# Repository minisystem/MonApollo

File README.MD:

=============================
Programmable Analog Monosynth
=============================
Prototype 
-------------
Digital Board
-------------

Digital board tested and working. SPI LED driving and switch reading tested. ADC pot reading but there is some cross-talk on
potentiometer ADC channels. Allowing sufficient settling time at ADC node between reads seems to mostly remedy this
to <= 1 LSB.

------------
Analog Board
------------
DAC S&H tested and working. There is some cross-talk (<= 10mV) on adjacent CV traces, but these are currently floating. Need to test
for crosstalk again once CV targets are installed.

NOISE/LFO/S&H tested and working, except for multiplexer latch problem mentioned below. Noise gain needed to be adjusted by
changing R180 to 10K and R181 to 750K (two 1.5M 0603s stacked in parallel). Also LFO module needede R3 (on module board) changed to 270K from 1M to get proper adjustment of sine/tri symmetry.
Sine symmetry is too 'pointy' on negative transition. Perhaps D1 and D2 need to be matched for Vf?

Bugs discovered thus far:

1. 7905 power regular pin error. Power supply rendered useless by this, so board requires external supply
2. LFO DG408 demultiplexer address lines are not latched, making LFO source addressing useless. Need to add 74LC75
latch in next revision.
2. C107 S&H sample cap footprint is 0805, but there are no NP0 or film caps in this footprint. Tried X7R and there was too much
droop. Through-hole film cap is in there now and droop is better, but still about 50-60 mV per second. This could be 
related to layout and leakage across PCB traces. A second look at layout shows definite room for improvement.
3. Glide circuit: Q6 PNP matched pair BCM857BS was flipped in schematic, swapping collectors and emitters. Good grief! Can't be salavaged
by a bodge, so will have to move on to VCO mod depth control and revisit glide in next PCB revision.
4. Glide slew caps C47 and C48 are currently 0603 but need to be 0805 or 1206 or even throughhole if film caps are to be used.

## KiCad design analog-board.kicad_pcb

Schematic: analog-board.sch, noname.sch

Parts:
C1, C8, C10, C18, C19, C20, C21, C22, C92, C93, C94, C96, C97, C98, C99, C103, C104: 1µ
C2, C9, C11, C15, C17, C23, C24, C25, C26, C27, C28, C29, C30, C31, C32, C33, C34, C35, C36, C37, C38, C39, C40, C41, C42, C43, C44, C45, C46, C85, C88, C114, C115, C117, C118, C119, C120, C121, C122, C123, C124, C125, C126, C127, C128, C129, C130, C131, C132, C133: 0.1µ
C3, C4, C5, C12, C13, C14, C16, C81, C82, C83, C84, C86, C87, C101: 10p
C6, C7: 5.6p
C47, C48: 470n
C49, C50, C51, C52, C53, C54, C55, C56, C57, C58, C59, C60, C61, C62, C63, C64, C65, C66, C67, C68, C69, C70, C71, C72, C73, C74, C75, C76, C77, C78, C79, C80: 0.01µ
C89, C91: 47μ
C90, C107: 100n
C95: 10μ
C100, C134: 22µ
C102: 4.7n
C105, C106, C108, C109: 1000µ
C110: 1.5n
C111: 100pF
C112, C113, C116: 2.2µ
C135: 47p
D1, D2, D3, D4, D5, D6, D7, D8, D9, D10: DIODE
D11, D12: LED
D13: 1N4148
EG1, EG2: EG
J1: AC IN
J2: OUT
J3: CONN_20X2
LFO1: VCO
P2: CONN_01X02
Q1, Q2, Q3, Q4, Q5, Q7, Q8, Q9, Q10, Q11, Q12, Q13, Q14, Q15, Q16, Q20: 2N3906
Q6: BCM857BS
Q17, Q18: NPN
Q19: J111
R1, R2, R3, R4, R5, R26, R27, R28, R29, R30, R79, R80, R95, R96, R97, R104, R110, R111, R112, R113, R130, R131, R132, R133, R134, R151, R183, R198: 12K
R6, R7, R8, R9, R13, R16, R17, R19, R20, R21, R87, R88, R89, R90, R98, R101, R114, R115, R118, R119, R122, R123, R124, R125, R135, R140, R188, R190: 510
R10, R11, R12, R24, R25, R91, R92, R102, R116, R117, R120, R121, R145, R174, R192: 2.2M
R14, R15, R18, R126, R127, R128, R129: 68K
R22, R23, R93, R94, R103, R146, R170, R171, R196: 18K
R31, R32, R33, R34, R38, R99, R100, R105, R136, R137, R138, R139, R152, R200: 47K
R35, R36, R37, R141, R142, R143, R144: 91K
R39, R189, R193, R206, R207: 1K
R40, R41, R42, R147, R148, R149, R150: 270K
R43, R44, R45, R46, R47, R48, R49, R50, R51, R52, R53, R54, R55, R56, R57, R58, R59, R60, R61, R62, R63, R64, R65, R66, R67, R70, R71, R72, R73, R74, R75, R77, R78, R81, R84, R153, R154, R155, R156, R157, R158, R159, R163, R164, R165, R167, R173, R175, R176, R184, R199, R202, R204: 100K
R68: 33K
R69: 1K 3300ppm/K
R76: 39K
R82, R83, R85, R86: 4.7K
R106, R107, R108, R109: 100K
R160, R205: 10K
R161: 3.3M
R162: 390K
R166, R168: 27K
R169: 680K**
R172: 47K
R177: 150K
R178: 22
R179, R185, R191, R201, R211, R213, R215: 10K
R180: 15K
R181, R203: 470K
R182: 120K
R186: 1.5K
R187, R195: 18K
R194: 20K
R197: 2.2meg
R208, R209: 220K
R210: 3.3K
R212, R214: 9.1K
R216: 270K
R217: 22K
TP1, TP2, TP3, TP4, TP5, TP6, TP7, TP8, TP9, TP10, TP11, TP12, TP13, TP14, TP15, TP16, TP17, TP18, TP19, TP20, TP21, TP22, TP23, TP24, TP25, TP26, TP27, TP28, TP29, TP30, TP31, TP32, TP33, TP34, TP35, TP36, TP37, TP38, TP39: CONN_1
TR1, TR2, TR3, TR4, TR5, TR8, TR9, TR10, TR11, TR12, TR13, TR14, TR15, TR16, TR18, TR19, TR21, TR23: 100K
TR6, TR7, TR17, TR20, TR22: 20K
U1, U2, U3, U18, U19, U29, U30, U32: LM13700
U4, U12: DG212B
U5, U8, U22, U23, U24, U25, U27, U28, U31, U33, U34, U35, U39: TL074-
U6: AD5556
U7, U15, U21, U26: TL072-
U9: AD8672
U10: ADR01
U11: DG212B; TSSOP-16
U13, U14, U16, U17, U45: DG408
U20: 74HC75
U36: 74LV573; Digikey SN74LV573APWR
U38, U41: 0 - 10V
U40: DG419
U42: 10 - 0V
U43: LM7812
U44: LM7912
U46: 7805
VCFA1: VCF_VCA
VCO1, VCO2: VCO

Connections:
+5V: C1.1 (+), C2.1, C88.1, C116.1 (+), TP35.1, U4.12 (VL), U6.28 (VDD), U11.12 (VL), U12.12 (VL), U20.5 (VCC), U36.20 (VCC), U40.5 (VCC), U46.3 (VO)
+12V: C8.1 (+), C9.1, C17.1, C18.1 (+), C21.1, C22.1, C25.1, C26.1, C27.1, C29.1, C31.1, C33.1, C35.1, C39.1, C40.1, C41.1, C43.1, C45.1, C85.1, C94.1, C97.1, C98.1, C104.1, C112.1 (+), C115.1, C118.1, C120.1, C122.1, C124.1, C126.1, C128.1, C130.1, C132.1, D9.2 (K), EG1.1 (V+), EG2.1 (V+), J3.1, J3.2, LFO1.2 (V+), R26.2, R27.2, R28.2, R29.2, R30.2, R76.2, R95.2, R96.2, R104.2, R130.2, R131.2, R133.2, R134.2, R151.2, R178.1, R184.1, R198.2, R206.1, R216.2, TP33.1, TR1.3, TR2.3, TR3.3, TR4.3, TR5.3, TR8.3, TR9.3, TR10.3, TR11.3, TR12.3, TR13.3, TR14.3, TR15.3, TR16.3, TR18.1, TR21.1, TR23.3, U1.11 (V+), U2.11 (V+), U3.11 (V+), U4.13 (V+), U5.4 (V+), U7.8 (V+), U8.4 (V+), U9.8 (V+), U10.3 (VIN), U11.13 (V+), U12.13 (V+), U13.13 (V+), U14.13 (V+), U15.8 (V+), U16.13 (V+), U17.13 (V+), U18.11 (V+), U19.11 (V+), U21.8 (V+), U22.4 (V+), U23.4 (V+), U24.4 (V+), U25.4 (V+), U26.8 (V+), U27.4 (V+), U28.4 (V+), U29.11 (V+), U30.11 (V+), U31.4 (V+), U32.11 (V+), U33.4 (V+), U34.4 (V+), U35.4 (V+), U39.4 (V+), U40.4 (V+), U43.3 (VO), U45.2 (EN), U45.13 (V+), U46.1 (VI), VCFA1.4 (V+), VCO1.2 (V+), VCO2.2 (V+)
-12V: C10.2 (-), C11.2, C19.1, C20.1, C23.1, C24.1, C28.2, C30.2, C32.2, C34.2, C36.2, C37.1, C38.1, C42.2, C44.2, C46.2, C93.1, C96.1, C99.1, C103.1, C113.2 (-), C114.1, C117.2, C119.2, C121.2, C123.2, C125.2, C127.2, C129.2, C131.2, C133.2, D10.1 (A), EG1.3 (V-), EG2.3 (V-), LFO1.3 (V-), R162.2, R207.2, R208.1, R209.1, TP34.1, TR1.1, TR2.1, TR3.1, TR4.1, TR5.1, TR8.1, TR9.1, TR10.1, TR11.1, TR12.1, TR13.1, TR14.1, TR15.1, TR16.1, TR18.3, TR19.1, TR21.3, TR23.1, U1.6 (V-), U2.6 (V-), U3.6 (V-), U4.4 (V-), U5.11 (V-), U7.4 (V-), U8.11 (V-), U9.4 (V-), U11.4 (V-), U12.4 (V-), U13.3 (V-), U14.3 (V-), U15.4 (V-), U16.3 (V-), U17.3 (V-), U18.6 (V-), U19.6 (V-), U21.4 (V-), U22.11 (V-), U23.11 (V-), U24.11 (V-), U25.11 (V-), U26.4 (V-), U27.11 (V-), U28.11 (V-), U29.6 (V-), U30.6 (V-), U31.11 (V-), U32.6 (V-), U33.11 (V-), U34.11 (V-), U35.11 (V-), U39.11 (V-), U44.3 (VO), U45.3 (V-), VCFA1.5 (V-), VCO1.3 (V-), VCO2.3 (V-)
/DAC0: J3.35, U6.6 (DB0)
/DAC1: J3.34, U6.5 (DB1)
/DAC2: J3.33, U6.4 (DB2)
/DAC3: J3.32, U6.3 (DB3)
/DAC4: J3.31, U6.2 (DB4)
/DAC5: J3.30, U6.1 (DB5)
/DAC6: J3.29, U6.27 (DB6)
/DAC7: J3.28, U6.26 (DB7)
/DAC8: J3.25, U6.25 (DB8)
/DAC9: J3.24, U6.24 (DB9)
/DAC10: J3.23, U6.23 (DB10)
/DAC11: J3.22, U6.22 (DB11)
/DAC12: J3.21, U6.21 (DB12)
/DAC13: J3.20, U6.20 (DB13)
/VREF: C15.1, TP9.1, U6.11 (R1), U10.4 (VOUT)
AMP LFO AMT CV: R146.1, U28.8, U28.9 (-)
ANALOG SW LATCH: J3.36, U36.11 (Load)
CUTOFF CV: R158.2, U28.1, U28.2 (-)
DAC MUX EN0: J3.19, U13.2 (EN)
DAC MUX EN1: J3.18, U14.2 (EN)
DAC MUX EN2: J3.17, U16.2 (EN)
DAC MUX EN3: J3.16, U17.2 (EN)
DB0: J3.8, U13.1 (A0), U14.1 (A0), U16.1 (A0), U17.1 (A0), U20.2 (D0), U36.2 (D0)
DB1: J3.9, U13.16 (A1), U14.16 (A1), U16.16 (A1), U17.16 (A1), U20.3 (D1), U36.3 (D1)
DB2: J3.10, U13.15 (A2), U14.15 (A2), U16.15 (A2), U17.15 (A2), U20.6 (D2), U36.4 (D2)
DB3: J3.11, U36.5 (D3)
DB4: J3.12, U36.6 (D4)
DB5: J3.13, U36.7 (D5)
DB6: J3.14, U36.8 (D6)
DB7: J3.15, U36.9 (D7)
EG1: EG1.6 (OUT), R154.2
EG1 ATT CV: EG1.10 (A), U33.1, U33.2 (-)
EG1 DEC CV: EG1.9 (D), U33.6 (-), U33.7
EG1 REL CV: EG1.8 (R), U33.13 (-), U33.14
EG1 SUS CV: EG1.7 (S), U33.8, U33.9 (-)
EG2: R3.1, R5.1, R111.1, U40.1 (COM)
EG2 ATT CV: EG2.10 (A), U34.1, U34.2 (-)
EG2 DEC CV: EG2.9 (D), U34.6 (-), U34.7
EG2 POL: J3.38, U40.6 (A/B)
EG2 REL CV: EG2.8 (R), U34.13 (-), U34.14
EG2 SUS CV: EG2.7 (S), U34.8, U34.9 (-)
EXT_CV_IN: R173.2, R199.2, TP38.1
FIL EG2 AMT CV: R127.1, U27.13 (-), U27.14
FIL LFO AMT CV: R128.1, U27.6 (-), U27.7
FIL OSCB AMT CV: R129.1, U27.1, U27.2 (-)
GATE: EG1.2 (GATE), EG2.2 (GATE), J3.3, TP39.1
GLIDE AMT CV: R68.2, U24.6 (-), U24.7
GND: C1.2 (-), C2.2, C8.2 (-), C9.2, C10.1 (+), C11.1, C15.2, C17.2, C18.2 (-), C19.2, C20.2, C21.2, C22.2, C23.2, C24.2, C25.2, C26.2, C27.2, C28.1, C29.2, C30.1, C31.2, C32.1, C33.2, C34.1, C35.2, C36.1, C37.2, C38.2, C39.2, C40.2, C41.2, C42.1, C43.2, C44.1, C45.2, C46.1, C47.2, C48.2, C49.2, C50.2, C51.2, C52.2, C53.2, C54.2, C55.2, C56.2, C57.2, C58.2, C59.2, C60.2, C61.2, C62.2, C63.2, C64.2, C65.2, C66.2, C67.2, C68.2, C69.2, C70.2, C71.2, C72.2, C73.2, C74.2, C75.2, C76.2, C77.2, C78.2, C79.2, C80.2, C85.2, C88.2, C89.2 (-), C90.2, C93.2, C94.2, C96.2, C97.2, C98.2, C99.2, C103.2, C104.2, C105.2 (-), C106.1 (+), C107.2, C108.2 (-), C109.1 (+), C112.2 (-), C113.1 (+), C114.2, C115.2, C116.2 (-), C117.1, C118.2, C119.1, C120.2, C121.1, C122.2, C123.1, C124.2, C125.1, C126.2, C127.1, C128.2, C129.1, C130.2, C131.1, C132.2, C133.1, D1.2 (K), D2.1 (A), D3.1 (A), D6.2 (K), D8.2 (K), D9.1 (A), D10.2 (K), D11.2 (K), D12.1 (A), EG1.4 (GND), EG2.4 (GND), J2.1, J3.39, J3.40, LFO1.1 (GND), LFO1.6 (GND), LFO1.10 (PWM), LFO1.12 (GND), Q1.2 (B), Q2.2 (B), Q3.2 (B), Q4.2 (B), Q5.2 (B), Q6.2 (B1), Q6.6 (C1), Q7.2 (B), Q8.2 (B), Q9.2 (B), Q10.2 (B), Q11.2 (B), Q12.2 (B), Q13.2 (B), Q14.2 (B), Q15.2 (B), Q16.2 (B), Q17.2 (B), Q17.3 (C), Q18.1 (E), Q20.2 (B), R6.1, R7.1, R8.1, R9.1, R13.1, R16.1, R17.1, R19.1, R20.1, R21.1, R31.1, R32.1, R33.1, R34.1, R38.1, R69.2, R87.1, R88.1, R89.1, R90.1, R98.1, R99.1, R100.1, R101.1, R105.1, R114.1, R115.1, R118.1, R119.1, R122.1, R123.1, R124.1, R125.1, R135.1, R136.1, R137.1, R138.1, R139.1, R140.1, R152.1, R160.1, R185.2, R186.2, R187.2, R188.1, R190.1, R193.2, R194.2, R200.1, R201.2, R205.2, R212.1, R214.1, R217.1, TP31.1, TP32.1, TP36.1, TP37.1, TR19.3, U4.5 (GND), U5.3 (+), U5.5 (+), U5.10 (+), U5.12 (+), U6.17 (MSB), U6.19 (GND), U7.3 (+), U7.5 (+), U8.3 (+), U8.5 (+), U8.10 (+), U8.12 (+), U9.3 (+), U9.5 (+), U10.2 (GND), U11.5 (GND), U12.5 (GND), U13.14 (GND), U14.14 (GND), U15.3 (+), U15.5 (+), U16.14 (GND), U17.14 (GND), U20.7 (D3), U20.12 (GND), U26.3 (+), U31.3 (+), U31.5 (+), U31.10 (+), U31.12 (+), U35.3 (+), U35.5 (+), U35.12 (+), U36.1 (OE), U36.10 (GND), U39.12 (+), U40.3 (GND), U40.7 (V-), U43.2 (GND), U44.1 (GND), U45.9 (S7), U45.10 (S6), U45.11 (S5), U45.14 (GND), U46.2 (GND), VCFA1.8 (GND), VCFA1.9 (GND), VCO1.1 (GND), VCO1.6 (GND), VCO1.12 (GND), VCO2.1 (GND), VCO2.6 (GND), VCO2.12 (GND)
KEYTRACK AMT CV: R126.1, U27.8, U27.9 (-)
LFO: J3.5, R1.1, R4.1, R112.1, R132.1, TP28.1, U45.8 (D)
LFO DMUX EN: J3.37, U20.4 (E23), U20.13 (E01)
LFO RATE CV: R176.2, U22.8, U22.9 (-)
LFO RESET: J3.7, LFO1.11 (SYNC)
LFO TUNE: J3.6, R215.1
NOISE: C101.2, R97.1, R181.1, R191.2, TP12.1, U39.14
NOISE MIX CV: R103.1, U23.6 (-), U23.7
unnamed: C3.1, R35.1, R40.2, U5.13 (-)
unnamed: C3.2, R40.1, R67.1, TP3.1, U5.14
unnamed: C4.1, R36.1, R41.2, U5.2 (-)
unnamed: C5.1, R37.1, R42.2, U5.9 (-)
unnamed: C6.1, U6.13 (REF), U9.1
unnamed: C6.2, U6.12 (RCOM), U9.2 (-)
unnamed: C7.2, U6.14 (IOUT), U9.6 (-)
unnamed: C12.1, R49.1, R53.2, U8.2 (-)
unnamed: C12.2, R53.1, R57.2, U8.1
unnamed: C13.1, R51.1, R54.1, U5.6 (-)
unnamed: C13.2, R54.2, R64.1, U5.7
unnamed: C14.1, R55.1, R61.2, U7.2 (-)
unnamed: C14.2, R61.1, U7.1, VCO1.10 (PWM)
unnamed: C16.1, R56.1, R62.2, U8.9 (-)
unnamed: C16.2, R62.1, U8.8, VCO2.10 (PWM)
unnamed: C47.1, U18.12, U21.3 (+)
unnamed: C48.1, U18.5, U21.5 (+)
unnamed: C81.1, R141.1, R147.2, U31.2 (-)
unnamed: C81.2, R147.1, R156.2, TP18.1, U31.1
unnamed: C82.1, R142.1, R148.2, U31.13 (-)
unnamed: C82.2, R148.1, R155.2, TP19.1, U31.14
unnamed: C83.1, R143.1, R149.2, U31.9 (-)
unnamed: C83.2, R149.1, R157.2, TP20.1, U31.8
unnamed: C84.1, R144.1, R150.2, U31.6 (-)
unnamed: C84.2, R150.1, R159.2, TP21.1, U31.7
unnamed: C86.1, R155.1, R156.1, R157.1, R158.1, R159.1, R162.1, R164.2, U35.6 (-)
unnamed: C86.2, R164.1, TP22.1, TR20.2, TR20.3, U35.7
unnamed: C87.1, R165.1, R167.2, U35.2 (-)
unnamed: C87.2, R167.1, R168.2, U35.1
unnamed: C89.1 (+), R172.1, R178.2, R179.1
unnamed: C90.1, R170.1, R171.2
unnamed: C91.1 (+), Q17.1 (E), R172.2
unnamed: C91.2 (-), Q18.2 (B), R177.2
unnamed: C92.1, VCFA1.1 (IN)
unnamed: C92.2, R109.2, TP30.1, U26.1
unnamed: C95.1 (+), Q18.3 (C), R177.1, R179.2, TP23.1
unnamed: C95.2 (-), R180.2
unnamed: C100.1 (+), C135.1, TP24.1, U26.5 (+), VCFA1.10 (OUT)
unnamed: C100.2 (-), R183.1
unnamed: C101.1, R180.1, R181.2, U39.13 (-)
unnamed: C102.1, LFO1.9, R210.2
unnamed: C102.2, R189.1
unnamed: C105.1 (+), C108.1 (+), D7.2 (K), D8.1 (A), P2.2, U43.1 (VI)
unnamed: C106.2 (-), C109.2 (-), D5.1 (A), D7.1 (A), U44.2 (VI)
unnamed: C107.1, Q19.1 (S), U39.5 (+)
unnamed: C110.1, R201.1, R203.2, U39.6 (-)
unnamed: C110.2, R203.1, TP27.1, U39.7, U45.12 (S4)
unnamed: C111.1, R202.2, R204.1, U35.13 (-)
unnamed: C111.2, R39.1, R204.2, U35.14
unnamed: C134.1 (+), R200.2, U32.5
unnamed: C134.2 (-), R202.1, TP26.1
unnamed: C135.2, D13.1 (A), U26.7
unnamed: D1.1 (A), D2.2 (K), R182.1, R187.1, U39.3 (+)
unnamed: D3.2 (K), R189.2, R194.1, U39.10 (+)
unnamed: D4.1 (A), Q19.3 (G), R197.2
unnamed: D4.2 (K), R215.2, TP25.1, U39.8
unnamed: D5.2 (K), D6.1 (A), J1.3
unnamed: D11.1 (A), R206.2
unnamed: D12.2 (K), R207.1
unnamed: EG2.5 (INV), U40.8 (A)
unnamed: EG2.6 (OUT), U40.2 (B)
unnamed: J1.1, P2.1
unnamed: J2.3, R39.2
unnamed: LFO1.4 (PITCH), R175.1, R176.1, TR22.1, TR22.2
unnamed: LFO1.5 (SCALE), LFO1.~ (SCALE), TR22.3
unnamed: LFO1.7, R182.2, U45.4 (S0)
unnamed: LFO1.8, U45.6 (S2)
unnamed: Q1.1 (E), R14.2
unnamed: Q1.3 (C), U1.16
unnamed: Q2.1 (E), R15.2
unnamed: Q2.3 (C), U1.1
unnamed: Q3.1 (E), R18.2
unnamed: Q3.3 (C), U2.16
unnamed: Q4.1 (E), R23.2
unnamed: Q4.3 (C), U3.1
unnamed: Q5.1 (E), R22.2
unnamed: Q5.3 (C), U3.16
unnamed: Q6.1 (E1), Q6.4 (E2), R76.1
unnamed: Q6.3 (C2), R81.2, R84.2
unnamed: Q6.5 (B2), R68.1, R69.1
unnamed: Q7.1 (E), R93.2
unnamed: Q7.3 (C), U19.16
unnamed: Q8.1 (E), R94.2
unnamed: Q8.3 (C), U19.1
unnamed: Q9.1 (E), R103.2
unnamed: Q9.3 (C), U2.1
unnamed: Q10.1 (E), R126.2
unnamed: Q10.3 (C), U29.16
unnamed: Q11.1 (E), R127.2
unnamed: Q11.3 (C), U29.1
unnamed: Q12.1 (E), R128.2
unnamed: Q12.3 (C), U30.16
unnamed: Q13.1 (E), R129.2
unnamed: Q13.3 (C), U30.1
unnamed: Q14.1 (E), R146.2
unnamed: Q14.3 (C), U32.16
unnamed: Q15.1 (E), R166.1
unnamed: Q15.3 (C), VCFA1.3 (RES)
unnamed: Q16.1 (E), R168.1
unnamed: Q16.3 (C), VCFA1.2 (AMP)
unnamed: Q19.2 (D), R191.1, R193.1, R197.1
unnamed: Q20.1 (E), R196.2
unnamed: Q20.3 (C), U32.1
unnamed: R1.2, R9.2, U3.3 (+)
unnamed: R6.2, R10.1, U1.14 (+)
unnamed: R10.2, TR1.2
unnamed: R7.2, R11.1, U1.3 (+)
unnamed: R11.2, TR2.2
unnamed: R8.2, R12.1, U2.14 (+)
unnamed: R12.2, TR3.2
unnamed: R5.2, R13.2, U3.14 (+)
unnamed: R2.2, R16.2, U1.13 (-)
unnamed: R3.2, R17.2, U1.4 (-)
unnamed: R4.2, R19.2, U2.13 (-)
unnamed: R20.2, R24.2, U3.4 (-)
unnamed: R21.2, R25.2, U3.13 (-)
unnamed: R24.1, TR4.2
unnamed: R25.1, TR5.2
unnamed: R26.1, U1.15
unnamed: R27.1, U1.2
unnamed: R28.1, U2.15
unnamed: R29.1, U3.2
unnamed: R30.1, U3.15
unnamed: R31.2, R35.2, U1.12
unnamed: R32.2, R36.2, U1.5
unnamed: R33.2, R37.2, U2.12
unnamed: R47.2, U4.7
unnamed: R48.2, U4.10
unnamed: R50.1, R55.2, TP6.1, U7.7
unnamed: R52.1, R56.2, TP7.1, U8.7
unnamed: R58.2, U4.2
unnamed: R60.2, U4.15
unnamed: R70.1, R71.1, R72.1, R77.2, U15.2 (-)
unnamed: R70.2, U11.10
unnamed: R71.2, U11.15
unnamed: R72.2, U11.2
unnamed: R73.1, R74.1, R75.1, R78.2, U15.6 (-)
unnamed: R73.2, U12.15
unnamed: R74.2, U12.2
unnamed: R75.2, U12.7
unnamed: R77.1, R79.1, TP10.1, U15.1
unnamed: R78.1, R80.1, TP11.1, U15.7
unnamed: R79.2, R87.2, U19.14 (+)
unnamed: R80.2, R88.2, U19.3 (+)
unnamed: R81.1, U18.16
unnamed: R82.2, U18.14 (+)
unnamed: R83.2, U18.13 (-)
unnamed: R84.1, U18.1
unnamed: R85.2, U18.3 (+)
unnamed: R86.2, U18.4 (-)
unnamed: R89.2, R91.2, U19.13 (-)
unnamed: R90.2, R92.2, U19.4 (-)
unnamed: R91.1, TR8.2
unnamed: R92.1, TR9.2
unnamed: R95.1, U19.15
unnamed: R96.1, U19.2
unnamed: R97.2, R98.2, U2.3 (+)
unnamed: R100.2, R108.1, TP16.1, U19.5
unnamed: R101.2, R102.2, U2.4 (-)
unnamed: R102.1, TR10.2
unnamed: R104.1, U2.2
unnamed: R105.2, R107.1, TP15.1, U2.5
unnamed: R99.2, R106.1, TP17.1, U19.12
unnamed: R106.2, R107.2, R108.2, R109.1, U26.2 (-)
unnamed: R110.2, R122.2, U29.13 (-)
unnamed: R111.2, R123.2, U29.4 (-)
unnamed: R112.2, R124.2, U30.13 (-)
unnamed: R113.2, R125.2, U30.4 (-)
unnamed: R114.2, R116.1, U29.14 (+)
unnamed: R115.2, R117.1, U29.3 (+)
unnamed: R116.2, TR11.2
unnamed: R117.2, TR12.2
unnamed: R118.2, R120.1, U30.14 (+)
unnamed: R119.2, R121.1, U30.3 (+)
unnamed: R120.2, TR13.2
unnamed: R121.2, TR14.2
unnamed: R130.1, U29.15
unnamed: R131.1, U29.2
unnamed: R132.2, R135.2, U32.14 (+)
unnamed: R133.1, U30.15
unnamed: R134.1, U30.2
unnamed: R136.2, R142.2, U29.12
unnamed: R137.2, R141.2, U29.5
unnamed: R138.2, R143.2, U30.12
unnamed: R139.2, R144.2, U30.5
unnamed: R140.2, R145.2, U32.13 (-)
unnamed: R145.1, TR15.2
unnamed: R151.1, U32.15
unnamed: R152.2, R153.2, U32.12
unnamed: R153.1, R154.1, R163.2, U35.9 (-)
unnamed: R160.2, R161.2, U35.10 (+)
unnamed: R161.1, TR16.2
unnamed: R163.1, R165.2, TP29.1, U35.8
unnamed: R166.2, TR17.3
unnamed: R169.1, R171.1, VCFA1.7 (FREQ)
unnamed: R169.2, TR18.2
unnamed: R170.2, TR20.1
unnamed: R57.1, R58.1, R59.1, R60.1, R173.1, TR7.1, TR7.2, VCO2.4 (PITCH)
unnamed: R174.1, VCFA1.6 (OFFSET)
unnamed: R174.2, TR21.2
unnamed: R175.2, TR19.2
unnamed: R183.2, R188.2, U32.3 (+)
unnamed: R184.2, R185.1, U39.9 (-)
unnamed: R186.1, R195.2, U39.2 (-)
unnamed: R190.2, R192.2, U32.4 (-)
unnamed: R192.1, TR23.2
unnamed: R195.1, U39.1, U45.5 (S1)
unnamed: R198.1, U32.2
unnamed: R63.2, R64.2, R65.2, R66.2, R67.2, R199.1, TR6.1, TR6.2, VCO1.4 (PITCH)
unnamed: R205.1, R216.1, U26.6 (-)
unnamed: R46.1, R47.1, R48.1, R52.2, R208.2, U8.6 (-)
unnamed: R43.1, R44.1, R45.1, R50.2, R209.2, U7.6 (-)
unnamed: R210.1, U45.7 (S3)
unnamed: R211.1, R212.2, U12.6
unnamed: R211.2, VCO2.9
unnamed: R213.1, R214.2, U11.3
unnamed: R213.2, VCO1.9
unnamed: TR6.3, VCO1.5 (SCALE), VCO1.~ (SCALE)
unnamed: TR7.3, VCO2.5 (SCALE), VCO2.~ (SCALE)
unnamed: U8.13 (-), U8.14
unnamed: U11.7, VCO1.11 (SYNC)
unnamed: U11.11, VCO1.7
unnamed: U11.14, VCO1.8
unnamed: U12.14, VCO2.7
unnamed: U20.10 (Q2), U45.1 (A0)
unnamed: U20.15 (Q1), U45.16 (A1)
unnamed: U20.16 (Q0), U45.15 (A2)
OSC EG2 AMT CV: R15.1, U24.13 (-), U24.14
OSC EG2 MOD: C4.2, R41.1, R66.1, TP4.1, U4.3, U5.1
OSC LFO AMT CV: R18.1, U22.6 (-), U22.7
OSC LFO MOD: C5.2, R42.1, R65.1, TP5.1, U4.14, U5.8
OSC PWM EG2 MOD: R38.2, R43.2, TP2.1, U3.12, U4.11
OSC PWM LFO MOD: R34.2, R45.2, TP1.1, U3.5, U4.6
OSC SYNC: U11.8, U36.16 (Q3)
OSCA FM AMT CV: R14.1, U22.13 (-), U22.14
OSCA GLIDE CV: R63.1, R83.1, R110.1, TP13.1, U21.1, U21.2 (-)
OSCA INIT CV: R51.2, U23.1, U23.2 (-)
OSCA MIX CV: R93.1, U25.6 (-), U25.7
OSCA PITCH CV: R82.1, U24.1, U24.2 (-)
OSCA PULSE: U11.1, U36.18 (Q1)
OSCA SAW: U11.16, U36.19 (Q0)
OSCA TRI: U11.9, U36.17 (Q2)
OSCB GLIDE CV: R59.2, R86.1, TP14.1, U21.6 (-), U21.7
OSCB INIT CV: R49.2, U25.8, U25.9 (-)
OSCB MIX CV: R94.1, U25.1, U25.2 (-)
OSCB MOD: U4.1, U4.8, U4.9, U4.16, U36.15 (Q4)
OSCB PITCH CV: R85.1, U24.8, U24.9 (-)
OSCB PULSE: U12.8, U36.14 (Q5)
OSCB SAW: U12.1, U36.13 (Q6)
OSCB SAW WAVE: R2.1, R113.1, U11.6, U12.3, VCO2.8
OSCB TRI: U12.16, U36.12 (Q7)
PWM A CV: R44.2, U23.13 (-), U23.14
PWM A EG2 AMT CV: R22.1, U22.1, U22.2 (-)
PWM A LFO AMT CV: R23.1, U23.8, U23.9 (-)
PWM B CV: R46.2, U25.13 (-), U25.14
RES CV: TR17.1, TR17.2, U28.6 (-), U28.7
SH0: C52.1, U13.4 (S0), U22.12 (+)
SH1: C51.1, U13.5 (S1), U22.10 (+)
SH2: C49.1, U13.6 (S2), U22.3 (+)
SH3: C50.1, U13.7 (S3), U22.5 (+)
SH4: C53.1, U13.12 (S4), U23.3 (+)
SH5: C54.1, U13.11 (S5), U23.5 (+)
SH6: C56.1, U13.10 (S6), U23.12 (+)
SH7: C55.1, U13.9 (S7), U23.10 (+)
SH8: C60.1, U14.4 (S0), U24.12 (+)
SH9: C59.1, U14.5 (S1), U24.10 (+)
SH10: C57.1, U14.6 (S2), U24.3 (+)
SH11: C58.1, U14.7 (S3), U24.5 (+)
SH12: C63.1, U14.12 (S4), U25.12 (+)
SH13: C64.1, U14.11 (S5), U25.10 (+)
SH14: C61.1, U14.10 (S6), U25.3 (+)
SH15: C62.1, U14.9 (S7), U25.5 (+)
SH16: C65.1, U16.4 (S0), U27.3 (+)
SH17: C66.1, U16.5 (S1), U27.5 (+)
SH18: C68.1, U16.6 (S2), U27.12 (+)
SH19: C67.1, U16.7 (S3), U27.10 (+)
SH20: C72.1, U16.12 (S4), U28.12 (+)
SH21: C71.1, U16.11 (S5), U28.10 (+)
SH22: C69.1, U16.10 (S6), U28.3 (+)
SH23: C70.1, U16.9 (S7), U28.5 (+)
SH24: C78.1, U17.4 (S0), U34.5 (+)
SH25: C77.1, U17.5 (S1), U34.3 (+)
SH26: C79.1, U17.6 (S2), U34.10 (+)
SH27: C80.1, U17.7 (S3), U34.12 (+)
SH28: C75.1, U17.12 (S4), U33.10 (+)
SH29: C76.1, U17.11 (S5), U33.12 (+)
SH30: C74.1, U17.10 (S6), U33.5 (+)
SH31: C73.1, U17.9 (S7), U33.3 (+)
TUNE: D13.2 (K), J3.4, R217.2
VDAC: C7.1, TP8.1, U6.9 (ROFS), U6.10 (RFB), U9.7, U13.8 (D), U14.8 (D), U16.8 (D), U17.8 (D)
VOL CV: R196.1, U28.13 (-), U28.14
~DAC RS: J3.26, U6.18 (~RS)
~DAC WR: J3.27, U6.15 (LDAC), U6.16 (~WR)

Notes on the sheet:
DG212 POWER CONNECTIONS
LFO SPEED INIT
Adjust R(Iabc) for unity gain
CV MIX OFFSET NULL
SELECTED
NP0 or FILM
LFO CLOCK
S&H OUT
S&H
PULSE
SAW
SINE
TRI
LFO + NOISE + S&H
SCALE TRIM
GLIDE
VCF CTRL offset
(+4V to -6V)
**may need to lower to 510K or 560K for 12V PWR
VCF CTRL input modified from Juno 106 VCF input for 0-10V response
ENVELOPE GENERATORS
ANALOG SWITCH LATCH
DAC BUS
S&H DECOUPLING
VDAC MULTIPLEXING
CV SAMPLE & HOLDS
DAC and DAC 10V reference
12V AC from wall adapter
POWER SUPPLY
NOISE + S&H from YUSYNTH LFO module is VCO SIP with 100nF integrator cap and 1nF FET reset cap
ADAPTED FROM SCI PROPHET 5 GLIDE CIRCUIT
*** PULSE FALLING EDGE THEN RISING EDGE SEE AD5556 DATASHEET
***
single turn
SPARE
A GND
D GND
SWITCH JUMPER
OP AMP and SWITCH DECOUPLING
EXT CV IN

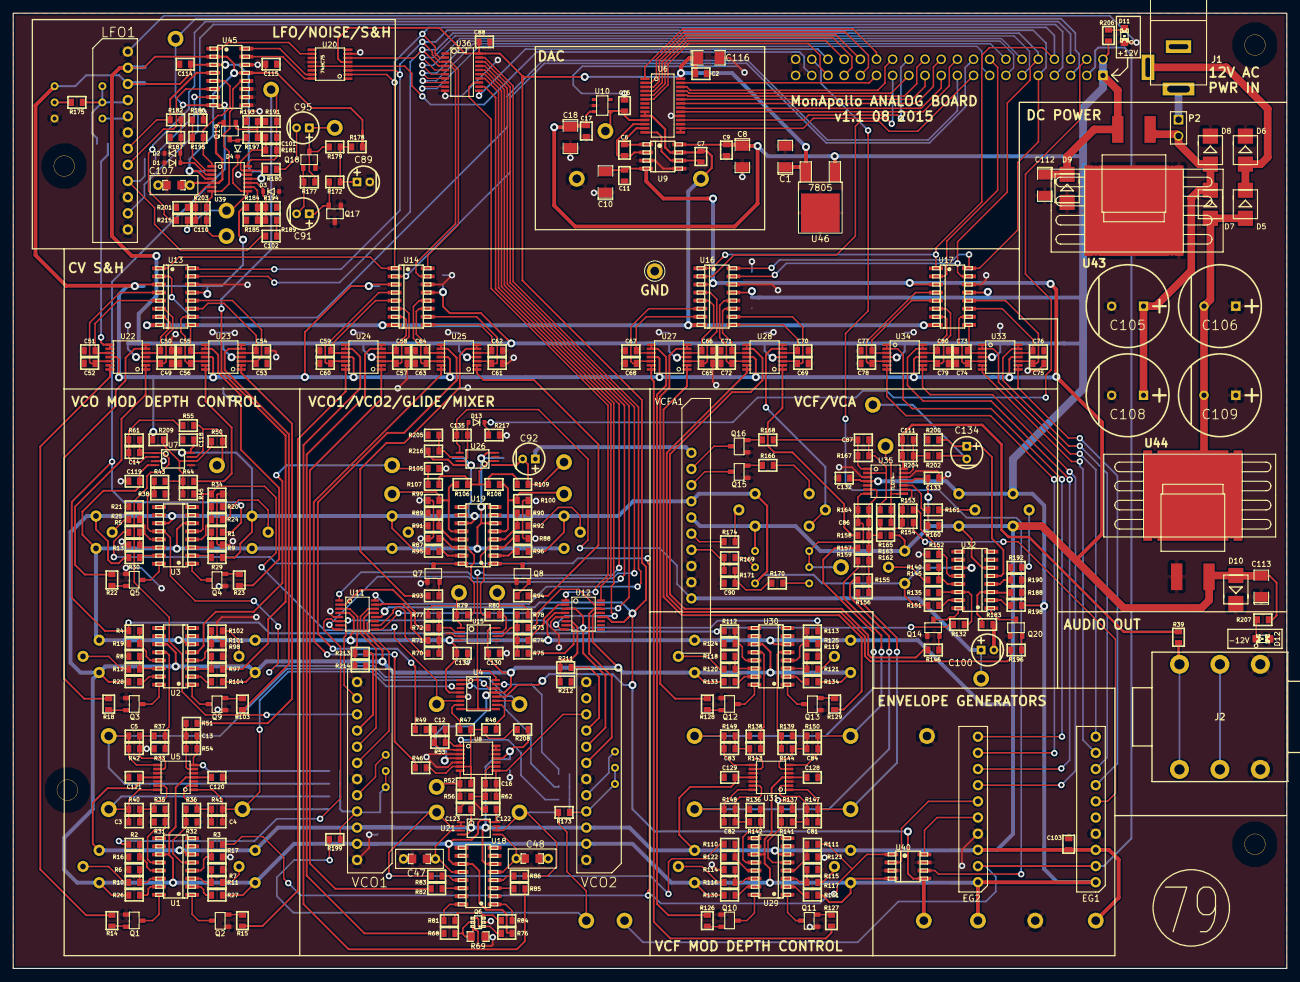
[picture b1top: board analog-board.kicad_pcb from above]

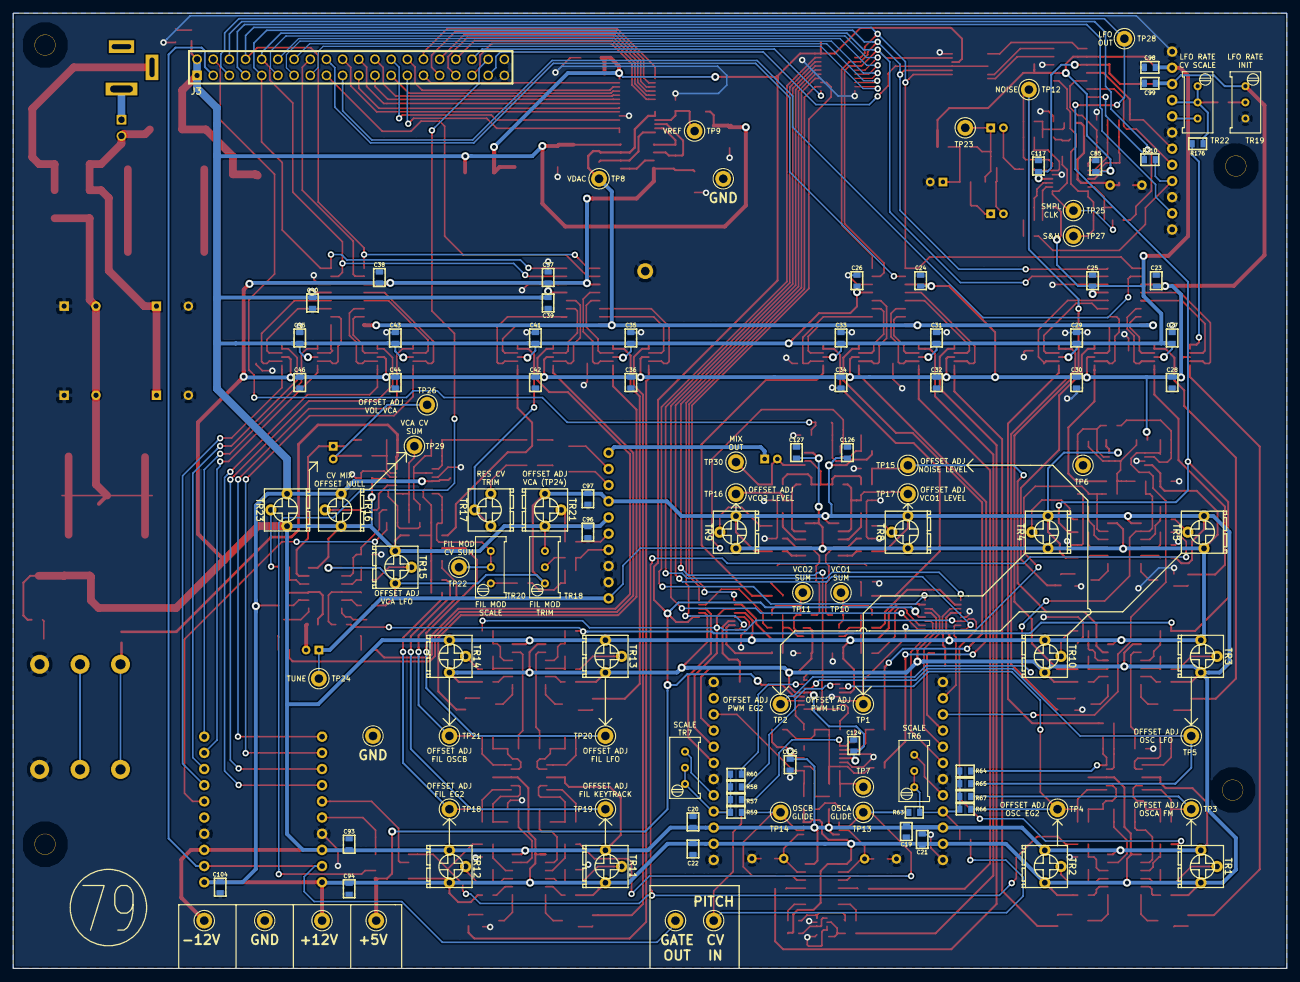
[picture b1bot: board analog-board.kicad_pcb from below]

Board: 2 copper layers, 200.0 x 150.0 mm, 506 parts (115 on the bottom side), 352 nets.

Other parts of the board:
HOLE-0.125-INCH, HOLE-0.125-INCH#2, HOLE-0.125-INCH#3, HOLE-0.125-INCH#4: VAL**; HOLE-0.125-INCH

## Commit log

2014-12-28 assigning footprints to digital board - in progress
2014-12-30 starting to layout digital brd
2015-01-01 finished pot/switch layout
2015-01-04 last commit before branch
2015-01-04 test led_rework commit
2015-01-06 working on 74AC595 LED arrays
2015-01-07 led and switch interfaces
2015-01-07 laying out board with led rework changes
2015-01-08 led driver layout
2015-01-09 LED array layout
2015-01-10 layout of switch interface
2015-01-11 laying out POT multiplexors
2015-01-11 all compoennts placed, time to start routing
2015-01-12 about to start routing
2015-01-12 bah problems with dsn export
2015-01-12 bah DSN export mess
2015-01-13 working on fixing DSN mess - mu symbols were the problem
2015-01-14 started routing with Kicad p&s router
2015-01-14 routing
2015-01-15 routing switches, LEDs and pots
2015-01-16 working on J1 and MCU connections for optimal routing
2015-01-17 almost done routing DAC and DATABUS to J1
2015-01-18 dac and databus routed
2015-01-19 changed TL1240 component and module pin numbering
2015-01-20 routing DS1 LED display
2015-01-21 just before first ses import
2015-01-21 autorouter almost done - just need to fix short complete traces to MCU
2015-01-21 more routing before autorouting. can't fix short trace incompletes on MCU pins
2015-01-22 more manual routing before autoroute
2015-01-23 manual routing before autoroute
2015-01-24 routed everything but power tracks
2015-01-24 finished routing and ground stitching
2015-01-26 main routing done. touch ups, adding decoupling
2015-01-26 touching up +5V power rail tracks
2015-01-27 added more decoupling caps and mounting holes
2015-01-28 next step: footprint testing and silkscreen
2015-01-29 last save before silk screen edit in 5112
2015-01-29 silkscreen editing in 5112
2015-01-31 fixed Alpha pot footprint
2015-02-10 updated MIDI conn footprint and 3D models
2015-02-11 finishing off silkscreen text, need to add GND test point
2015-02-12 GND test points added, more silkscreen work
2015-02-13 more silkscreen work almost ready to order
2015-02-13 routing, silkscreen and tweaking done, about to try to change SPI_EN on 595s
2015-02-14 just adding 5112 gerbers. 5365 gerber output has drill hole bug
2015-02-15 spi_en added to all 595s
2015-02-16 ready to order
2015-02-16 v1.0 sent for fabrication
2015-02-18 component placement for analog board
2015-02-18 analog board component placement
2015-02-20 analog board component placement. problem with tssop-14 footprint. public kicad github repository seems to have dropped this footprint
2015-02-21 updated D2PAK footprints, fixed missing TSSOP-14 footprint
2015-02-22 starting to route, still need to place S&H buffers. VCO1 and VCO2 outputs to DG212s need to be swapped for better layout
2015-02-25 routing S&H and CV traces
2015-02-26 moved audio jack, about to move DAC dmuxers and S&H components
2015-02-26 routing, moving stuff around to redo DAC demux placement and routing and S&H placement and routing
2015-02-27 moved S&H and DAC demuxers, routed 16 of 32 CVs
2015-03-02 routed all CVs still need to route EG1 EG2 S&Hs
2015-03-02 component placement done. need to add more bypass caps and route power traces
2015-03-03 added decoupling caps for op amps, need one more pair. started routing power. Oh boy...
2015-03-04 almost done routing pos and neg 12V power traces, but 5V traces are provign difficult. Going to branch now and start over again routing power traces first
2015-03-04 pulled up all traces, made a few minor placement changes, will now start routing power traces
2015-03-04 starting routing 12V power traces bus style, linking throughhole trimmer pins
2015-03-05 still routing
2015-03-05 starting to route CV VCA traces
2015-03-05 commit before lunch
2015-03-06 routing LFO-NOISE-S&H
2015-03-06 routing VDAC sample and holds and multiplexors
2015-03-07 routing S&H CV traces. Need to move U14 over to the left to shorten 7 out of 8 CV traces
2015-03-09 routing routing routing
2015-03-10 all CVs routed, just need to adjust EG1 and EG2 CVs
2015-03-10 flippled main 40 pin connector to work with connector on digital board - reconnected all traces
2015-03-12 getting close to finishing routing signal and power traces
2015-03-13 all power and signal traces routed, need to connect outstanding grounds and fix a few routing misconnects
2015-03-13 stitching grounds
2015-03-14 stiching grounds, will need to move LFO SIP module
2015-03-14 10 more traces to route
2015-03-14 all routed, need to tweak and move LFO module
2015-03-14 routed, still tweaking
2015-03-15 routing done, still some tweaking to do, 3D render is almost done
2015-03-15 test ssh
2015-03-15 added more test points, including power input points
2015-03-15 a little more tweaking to be done. Need to consider ferrite beads on power supply
2015-03-17 more tweaking finished, not much left to do. fixed VCO outline orientation - the bulk of the mold was on the wrong side in the module footprint
2015-03-21 made a few changes to digital board for 3D rendering
2015-03-22 changes to analog board for better 3D representation, plus moved sample and hold noise source caps down to clear MIDI jack on digital board in final pcb assembly
2015-03-26 about half done silkscreen cleanup. Still need to add 1V/oct CV input on pitch summer
2015-03-26 adding external CV and GATE input test points
2015-03-26 CV and GATE test points added and routed
2015-03-26 adjusted EXT CV input to VCO1, more silkscreen work
2015-03-27 silkscreen top layer mostly done, need to do bottom layer next
2015-03-27 started silkscreen polishing on bottom layer
2015-03-27 bottom layer silkscreen work
2015-03-28 bottom silkscreen labelling of test points
2015-03-28 silkscreen work done. Do footprint check and then order board
2015-03-28 more silkscreen touchups. about to check footprints
2015-03-30 routing and silkscreen done. need to check footprints next
2015-03-30 fixed 7805 DPAK footprint, fixed DG212 pin swap. footprints checked, ready to order
2015-03-30 ignoring analog-board in Gerbers folder for now, will add once PCB ordrerd. Just restored digital-board folder in Gerbers folder
2015-03-30 ready to plot analog gerbers
2015-03-31 enlarged pol cap holes, they were too small. about to order PCB
2015-05-21 last commit before changing PCB errors in revision 1.0. Discovered thus far: 7905 -ve power regulator pins are incorrect, so whole power section is useless in this version. LFO demultiplexer doesn't 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
2015-05-21 added readme.md
2015-05-21 revised readme.md
2015-05-22 added 74HC75 LFO demux latch and fixed 7912 negative voltage regulator pin out. Not finished routing new changes
2015-05-24 74LC75 quad latch added and routed. Probably need to change layout of S&H circuit as there is droop
2015-05-24 added footprint note changes to schematic
2015-05-24 fixed Q6 swap in schematic and rerouted
2015-05-25 shuffled U13 and U14 group S&H/CV traces a bit to try to reduce coupling. Hardly enough room to do anything meaningful
2015-05-29 fixed R73 and R78 label swap on PCB silkscreen. Added notes to schematic about changing feedback resistor value to reduce gain of waveform and summing mixers
2015-06-21 added some notes to schematic about capacitor packages and values based on evalutation of v1.0 analog board
2015-06-21 changed C47, C48 and C107 packages to 5mm box/0805 combos
2015-06-22 add 220K resistors to PWM LFO modulation summer to balance LFO waveform around 0V
2015-06-22 added resistor dividers for pulse output on VCOs and LFO to get 10Vpp pulse level
2015-07-02 added a few notes to digital board schematic
2015-07-07 LFO TUNE now connected to S&H clock through R215
2015-07-07 moved final DC blocking cap to output of volume VCA, deleted ring output resistor to J2
2015-07-30 added note about changing R11 and R117 to 470K for VCO1 and FIL cutoff modulation by EG2
2015-08-01 added TUNE COMPARATOR in schematic, need to route in PCB
2015-08-04 routed tune comparator
2015-08-05 moved U36 and U46 from bottom side of board to top side, routed, adjusted routing and labels. Q36 footprint triple checked now
2015-08-06 basically done. need to do last quick check of a few footprints, but otherwise board is ready to order. Will place order upon returning from Lighthouse
2015-08-11 few touch ups and silkscreen corrections. Ready to order from Seeed Studio
2015-09-12 just added a few notes about removing filter pitch depth control VCA and maybe repurposing OTA for Mike Simms dual OTA VCA for final volume VCA
2015-09-18 couple of notes added - power supply is WRONG and needs to be revised. Thermal vias for L7912 and L7812 need to be added and U36 package needs to be adjusted
2015-09-22 few changes to schematic not implemented in board yet to refelct hacks to analog board v1.1
2015-09-24 tiny changes to silkscreen and hidden value positions to make pcb file easier reference for building
